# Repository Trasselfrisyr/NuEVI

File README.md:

### ⚠️ ORIGINAL REPO HAS BEEN MOVED TO BERGLUNDINST ORGANISATION ⚠️

This repository exists for archival purposes. Please update any references/links to https://github.com/berglundinst/NuEVI instead.

# NuEVI
A project by wind controller enthusiasts wanting to save the endangered Electronic Valve Instrument.

Follow the project at https://hackaday.io/project/25756-diy-evi-style-windcontroller

## Building NuEVI

NuEVI is easiest to build using the Arduino IDE. You will also need to download and install
[Teensyduino](https://www.pjrc.com/teensy/td_download.html) to build for and upload to the Teensy.

### Libraries

A few libraries need to be added that are not part of the default Arduino install. These can be
added directly via the Library Manager in the Arduino IDE:
* Adafruit MPR121
* Adafruit GFX
* Adafruit SSD1306 (version 1.2.9 or above)
* NuEVI also includes on the [Filters](https://github.com/JonHub/Filters) library by Jonathan Driscoll, but that is no longer an external dependency.

### Compile options

Open NuEVI.ino in the Arduino IDE. Under "Tools -> Board", select "Teensy 3.2 / 3.1". Then set
"Tools -> USB Type" to "MIDI".

### Building and uploading

Connect the NuEVI via USB to your computer, open the Teensy application and make sure the "Auto"
option is selected (the green round icon). In Arduino IDE, select "Sketch -> Verify/Compile" and
once that is complete press the reset button on the Teensy chip (you have to remove the top cover
on the NuEVI to access this). Upon resetting, it should upload the new firmware onto the NuEVI.

After uploading new firmware, you may need to reset the config memory of the NuEVI. To do this, press
and hold the MENU and ENTER buttons while turning on the NuEVI. Note that this resets all sensor calibrations too. For new versions this should not be neccessary, as value and version checks are in place.

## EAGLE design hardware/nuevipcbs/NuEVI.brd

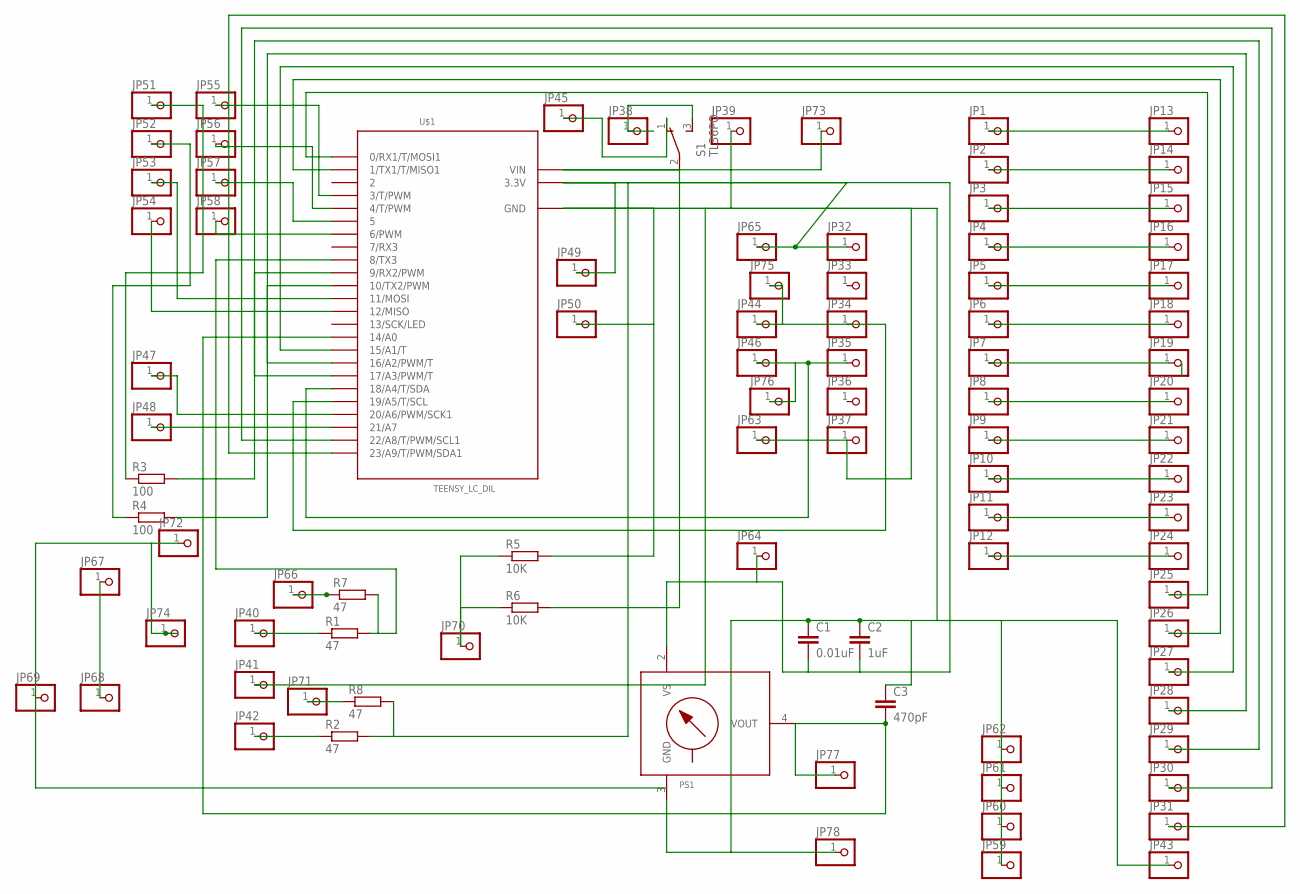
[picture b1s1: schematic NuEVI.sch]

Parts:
C1: 0.01uF; C050-024X044
C2: 1uF; C050-024X044
C3: 470pF; C050-024X044
JP1, JP2, JP3, JP4, JP5, JP6, JP7, JP8, JP9, JP10, JP11, JP12, JP13, JP14, JP15, JP16, JP17, JP18, JP19, JP20, JP21, JP22, JP23, JP24, JP25, JP26, JP27, JP28, JP29, JP30, JP31, JP32, JP33, JP34, JP35, JP36, JP37, JP38, JP39, JP40, JP41, JP42, JP43, JP44, JP45, JP46, JP47, JP48, JP49, JP50, JP51, JP52, JP53, JP54, JP55, JP56, JP57, JP58, JP59, JP60, JP61, JP62, JP63, JP64, JP65, JP66, JP67, JP68, JP69, JP70, JP71, JP72, JP73, JP74, JP75, JP76, JP77, JP78: PINHD-1X1; 1X01
PS1: MPX-1369; 1369
R1, R2, R7, R8: 47; 0207/7
R3, R4: 100; 0207/7
R5, R6: 10K; 0207/7
S1: TL36PO; TL3XPO
U$1: TEENSY_LC_DIL; TEENSY_3.0-3.2&LC_DIL

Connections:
GND: C1.1, C2.1, C3.1, JP37.1, JP39.1, JP41.1, JP43.1, JP50.1, JP59.1, JP60.1, JP61.1, JP62.1, JP63.1, JP69.1, JP72.1, JP74.1, JP78.1, PS1.3 (GND), R5.2, U$1.AGND (GND), U$1.GND
unnamed: JP1.1, JP13.1
unnamed: JP2.1, JP14.1
unnamed: JP3.1, JP15.1
unnamed: JP4.1, JP16.1
unnamed: JP5.1, JP17.1
unnamed: JP6.1, JP18.1
unnamed: JP7.1, JP19.1
unnamed: JP8.1, JP20.1
unnamed: JP9.1, JP21.1
unnamed: JP10.1, JP22.1
unnamed: JP11.1, JP23.1
unnamed: JP25.1, U$1.0 (0/RX1/T/MOSI1)
unnamed: JP12.1, JP24.1
unnamed: JP26.1, U$1.1 (1/TX1/T/MISO1)
unnamed: JP27.1, U$1.15/A1 (15/A1/T)
unnamed: JP28.1, U$1.16/A2 (16/A2/PWM/T)
unnamed: JP29.1, U$1.17/A3 (17/A3/PWM/T)
unnamed: JP30.1, U$1.22/A8 (22/A8/T/PWM/SCL1)
unnamed: JP31.1, U$1.23/A9 (23/A9/T/PWM/SDA1)
unnamed: C1.2, C2.2, JP32.1, JP49.1, JP64.1, JP65.1, PS1.2 (VS), R2.2, R8.2, U$1.3.3V
unnamed: JP47.1, U$1.20/A6 (20/A6/PWM/SCK1)
unnamed: JP34.1, JP44.1, JP75.1, U$1.19/A5 (19/A5/T/SCL)
unnamed: JP35.1, JP46.1, JP76.1, U$1.18/A4 (18/A4/T/SDA)
unnamed: JP38.1, S1.3 (S)
unnamed: R1.2, R7.2, U$1.8 (8/TX3)
unnamed: JP40.1, R1.1
unnamed: JP42.1, R2.1
unnamed: C3.2, JP77.1, PS1.4 (VOUT), U$1.14/A0
unnamed: JP73.1, R6.2, S1.2, U$1.VIN
unnamed: JP48.1, U$1.21/A7
unnamed: JP51.1, R3.1
unnamed: JP52.1, R4.1
unnamed: JP53.1, U$1.11 (11/MOSI)
unnamed: JP54.1, U$1.12 (12/MISO)
unnamed: JP55.1, U$1.3 (3/T/PWM)
unnamed: JP56.1, U$1.4 (4/T/PWM)
unnamed: JP57.1, U$1.5
unnamed: JP58.1, U$1.6 (6/PWM)
unnamed: JP45.1, S1.1 (O)
unnamed: R4.2, U$1.10 (10/TX2/PWM)
unnamed: JP67.1, JP68.1
unnamed: R3.2, U$1.9 (9/RX2/PWM)
unnamed: JP70.1, R5.1, R6.1
unnamed: JP71.1, R8.1
unnamed: JP66.1, R7.1

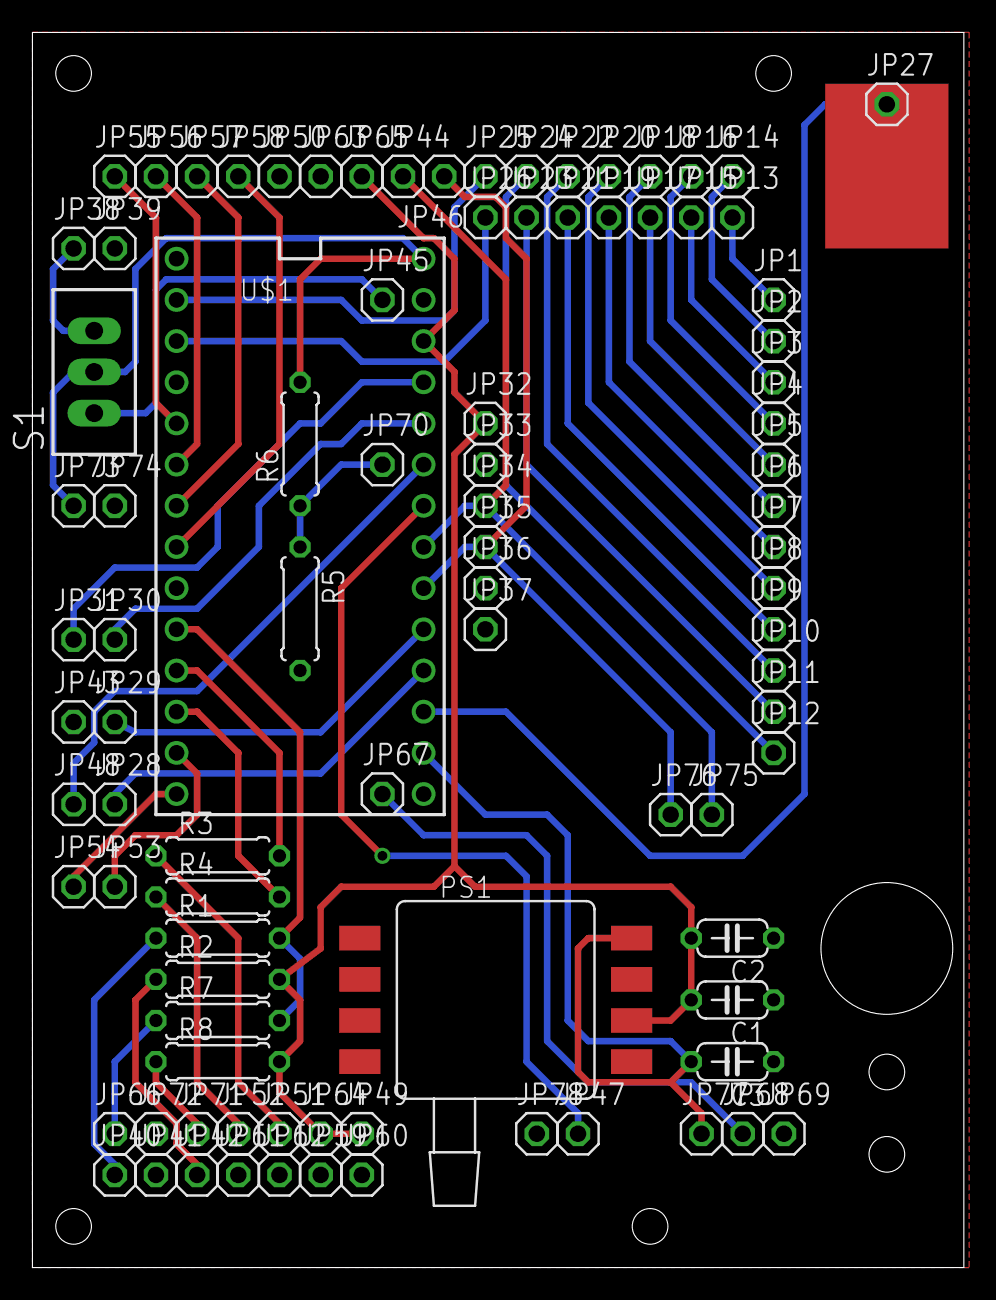
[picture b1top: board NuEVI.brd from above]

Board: 2 copper layers, 57.5 x 76.2 mm, 92 parts (0 on the bottom side), 46 nets.

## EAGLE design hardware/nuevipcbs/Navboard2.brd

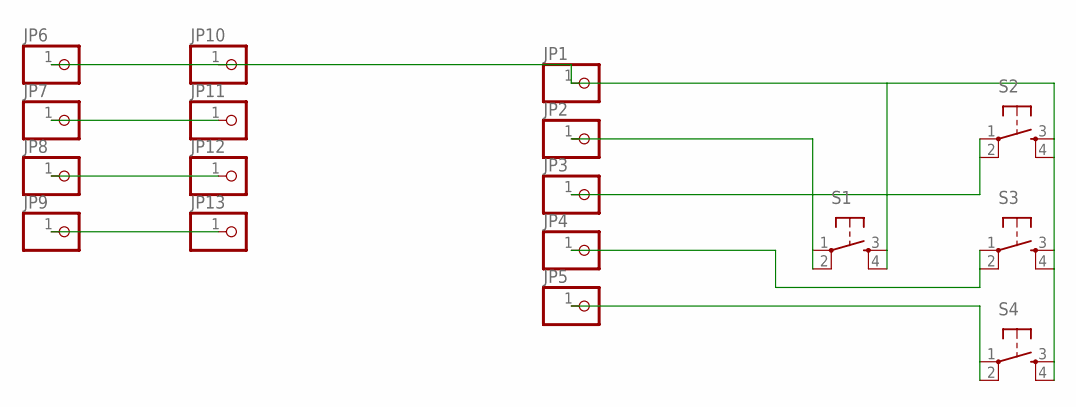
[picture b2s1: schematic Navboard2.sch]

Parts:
JP1, JP2, JP3, JP4, JP5, JP6, JP7, JP8, JP9, JP10, JP11, JP12, JP13: PINHD-1X1; 1X01
S1, S2, S3, S4: TAC_SWITCHPTH; TACTILE-PTH

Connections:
GND: JP1.1, JP6.1, JP10.1, S1.3, S1.4, S2.3, S2.4, S3.3, S3.4, S4.3, S4.4
unnamed: JP2.1, S1.1, S1.2
unnamed: JP3.1, S2.1, S2.2
unnamed: JP4.1, S3.1, S3.2
unnamed: JP5.1, S4.1, S4.2
unnamed: JP7.1, JP11.1
unnamed: JP8.1, JP12.1
unnamed: JP9.1, JP13.1

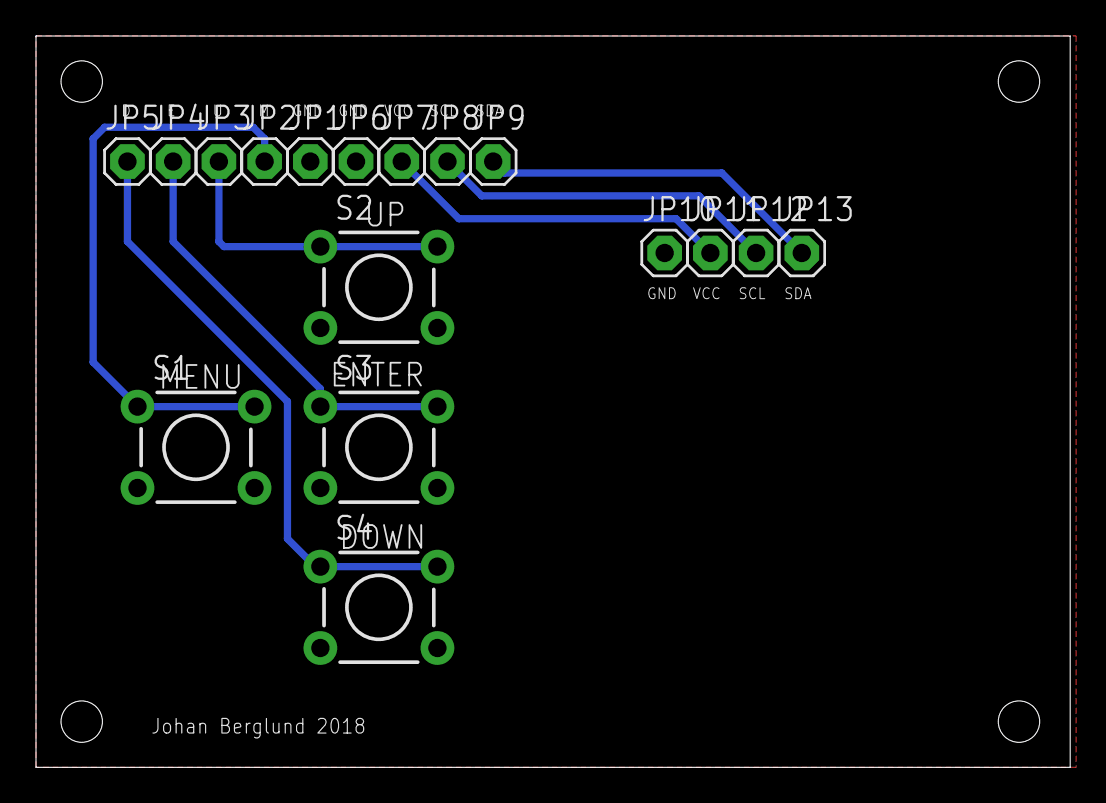
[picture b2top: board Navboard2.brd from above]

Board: 2 copper layers, 57.5 x 40.6 mm, 17 parts (0 on the bottom side), 8 nets.

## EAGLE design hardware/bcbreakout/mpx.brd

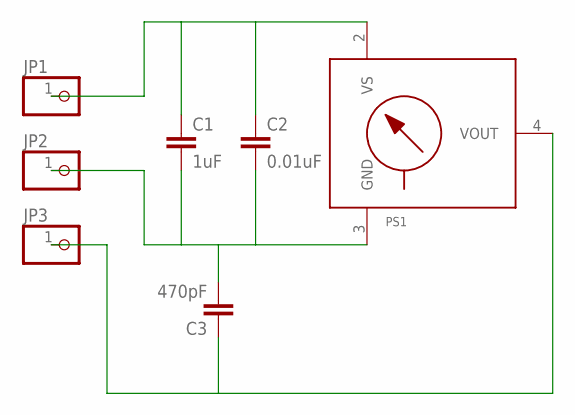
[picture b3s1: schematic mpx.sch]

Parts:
C1: 1uF; C050-024X044
C2: 0.01uF; C050-024X044
C3: 470pF; C050-024X044
JP1, JP2, JP3: PINHD-1X1; 1X01
PS1: MPX-1369; 1369

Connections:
GND: C1.2, C2.2, C3.2, JP2.1, PS1.3 (GND)
unnamed: C3.1, JP3.1, PS1.4 (VOUT)
unnamed: C1.1, C2.1, JP1.1, PS1.2 (VS)

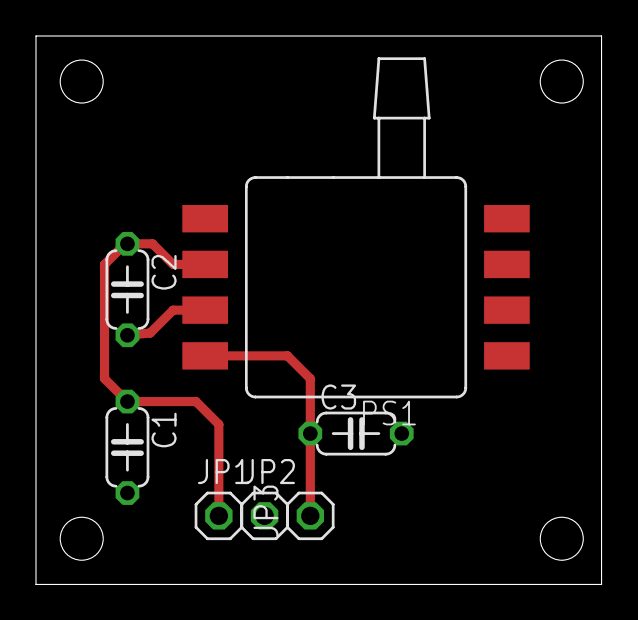
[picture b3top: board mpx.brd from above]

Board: 2 copper layers, 31.4 x 30.5 mm, 7 parts (0 on the bottom side), 3 nets.

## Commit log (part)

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2017-08-08 First commit. Arduino sketch plus devboard plans.
2017-08-09 Added the option to have the vibrato go down first, then up.
2017-08-26 Added untested version with menu system and other added features. Preview.
2017-08-29 Bugfixes galore. Added sensor level indicators in sensor adjust settings. Added MIDI note range check with octave repeat.
2017-09-09 Disabled baseline tracking for the MPR121. Added status LEDs for breath and bite (portamento).
2017-09-11 More work on the vibrato. Fixed sending program change to wrong channel on DIN MIDI. Pitchbend start value fix.
2017-09-16 Breath reading changed from 10 bit to 12 bit. Added hi res midi on cc#1 (mod) and an option to compile with breath CV output on DAC pin. Special key functions implemented (slur sustain, parallel chor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
2017-09-23 Just forgot a thing for the slurred note velocity.
2017-10-03 Added more breath response curve options.
2017-10-05 Adjusted some curves where values were a bit off. Replaced the S-curves with less dramatic ones. Added a fourth one.
2018-02-28 Added battery voltage meter (matched 10K resistors to A11 from AGND and VIN). Added CC#74 as option for extra controller. Added velocity sample delay setting and velocity bias setting. Removed midi p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
2018-04-19 Got the more advanced breath signal filtering working. (Still some commented out crap in there from testing/comparing. Just ignore it.) Fixed some errors in curves.
2018-05-25 Added chord rotator function. Added setting for mono voice note during chord play. Minor enhancements in FastPatch functionality. Bug fix for storing AT setting.
2018-08-27 New and improved vibrato. Added vibrato menu for setting depth, sensitivity and zero return speed. Added Gate Hold function. Added negative pressure trig for legacy instant settings functionality. Bu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
2018-08-28 Update readme
    Add notice about resetting EEPROM config.
2018-09-01 Added item in vibrato menu for setting squelch level for vibrato sensor (noise filtering/dead zone). Added setting for vibrato direction.
2018-09-03 Use defines instead of hardcoded pin numbers Also automatic "dangling whitespace" cleanup
2018-09-03 Check for exact display type instead of just height
2018-09-03 Refactor factory reset for clarity
2018-10-22 Version 1.2.7
2018-10-27 Version 1.2.9
    * Fix for pitch bend summing near zero.
    * Deglitch setting now in steps of 1ms
    * Velocity sample delay setting now in steps of 1ms
2018-12-28 Added anti-glitch for top roller when in bottom octave. Added individual note-offs efter All Notes Off at MIDI Panic (to work in Logic and other software not recognizing the regular All Notes Off).
2019-03-02 Use midi serial definition from proper place
2019-03-02 A whiter shade of space
2019-03-02 Constrain unconstrained non-use of constrain()
2019-03-04 Output breath sensor value on DAC (from Johan)
2019-03-04 Move all source files to subdirectory to be less confusing for Arduino IDE
2019-03-04 Rename non-main ino files to cpp
2019-03-05 Let us not rename files right now.
    This reverts commit 347b6e5c71ea4c537caaec08537b96d3f825ece0.
2019-03-21 Cleanup
2019-06-03 Renamed menu.ino to menu.cpp
    This change required lots of other changes to have it compile. I had to declare all variables from NuEVI.ino used by the menu as extern in a separate header file (globals.h).
    Also I moved all defines from NuEVI.ino to a config.h file. I think some of these could be moved back or even moved into menu.cpp.
    I declared many variables and functions in menu.cpp as static and moved them around to avoid forward declarations. For simplicity I did some forward declarations anyway.
    Some varibles only used in menu.cpp was moved from NuEVI.ino instead of having them as externals.
2019-06-07 Fix problem where the V was still visible if battery low
2019-06-08 Move access to usbMIDI to midi.ino
    NuEVI.ino shouldn’t have to know about usbMIDI.
2019-06-13 Simple simulation code
    Builds a native program on MacOS that runs the NuEVI firmware compiled for x86_64.
    Only input is arrow keys for menu buttons for now. Only output is console and display.
    Copied some more library files into the simulation folder, and renamed the modified *.cpp files from the libraries to *_sim.cpp.
2019-06-21 More inputs and outputs added in simulator
    * Set default value for battery sensor input
    * Show EEPROM values as unsigned.
    * Simulate K1 to K7 inputs (valve and trills++)
2019-06-21 Fixed spelling
2019-06-22 Initialize touch inputs to untouched
2019-06-23 Write new factor constants even if old version was < 24
    This bug would probably never happen in real life, and could be fix by holding down menu and enter buttons at startup. But a bug is a bug.
    The only reason I found this bug is that the simulator didn’t initialise EEPROM to 0xff, and even after I did that it crashed, because a version of 0xffff wasn't handled.
2019-06-23 Advanced unusage of parameters
2019-06-23 Minor cleanups
2019-06-23 Removed an unused function
2019-06-23 Menu selection is now data driven
    Some major refactoring has been going on.
    Added simple structs of data containing info about what action to take when a menu item is selected.
    Finally removed all but one call to display.display() in menu-function. There might still be more than one call to it on a frame though, since some functions still calls it internally.
2019-06-23 Use helper function for midi channel as well
2019-06-23 Handle sub menus in a generic way and moved adjust menu logic to separate file
    This is a big one where I can finally reap what I sown. Sub menu entries now provide two functions, one to get the text for the current value and one to apply changes aka save to EEPROM. With this I 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
    The question is still what to do with less general menus like the rotator and fast patch menu.
    One problem with the current implementation is that it is RAM heavy. It seems the const MenuEntry structs are placed
2019-06-23 Unified main and patch menu input handling
    Now all menu pages are handled the same way, which is great because now I can implement scrolling in the menu pages.
2019-06-23 Two unrelated changes
    * Move text print of submenu into function
    * No need to check if value changed since writeSettings uses EEPROM.update.
2019-06-23 Small bug fix
2019-06-23 Pass *currentPage to functions instead of the original page data
    This way it will be easier to break out even more functionality into more general functions.
2019-06-23 Moved over the rotation menu to new system
    Had to change how the values where stored in RAM from singed to unsigned to be able to use the generic menu features. Also had to add the MenuEntrySub as a parameter to the menu callback functions to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
    Did some major cleanup now that the special case of rotator menu is gone together with all uses of the old version of the sub menu struct.
2019-06-23 Converted more of the sub menus to the new sub definitions
    Found out that it’s the lambda functions used for pointer that forces the structs to be in ram instead or rom.
2019-06-23 Add argument parsing for eeprom stuff
2019-06-23 Converted lambdas to normal functions to save RAM
2019-06-24 EEPROM file storage, and argparsing that actually works
2019-06-24 Check for correct target platform and USB type
2019-06-24 Allow midi+serial usb type too (useful for "console debugging")
2019-06-24 Only write to file if value has actually changed.
2019-06-25 Annotate "fingering math" for readability
2019-06-25 Use pin names rather than hardcoding
2019-06-25 Removed switch statement for curves, use array lookup instead
2019-06-26 Fixed regression bug for patch select
    After the menu refactoring, switching patch with up/down buttons when screen was off didn't work correctly. Now it should work like before i.e. switch patch on first press of button and not requiring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
2019-06-27 Only handle scrolling if there are items to scroll
2019-07-15 EXTRAS menu page added, with items LEGACY PB, LEGACY BR, GATE HOLD and SPECIAL KEY to enable/disable these special functions.
2019-07-17 Flush screen buffer to the display in adjust menu
    The return value (that flagged for redraw) was ignored when handling input in the adjust menu.
2019-07-18 Removed SR and SR+ from CC list
2019-07-23 Remove global var for wireless power, add wl channel menu
2019-07-24 Added newer version hex files.
2019-07-25 Define constant for "dipswitch" positions
2019-07-25 Move EEPROM read/write functions to settings
2019-07-26 Simplify readSwitches()
2019-07-26 Mistakes were made
2019-07-27 Incorporate Filters code into NuEVI repo for smoother setup.
2019-07-28 Needs more whitespace
2019-07-30 Add facility to receive config via sysex
2019-08-04 Actually match teensy/arduino signatures
2019-08-05 Add functionality to use files as MIDI data to send to simulated device
2019-08-07 Try to core midi
2019-08-07 Make nuevisim compile again. And send midi noteOn.
2019-08-15 Proper bounds for breath cc value
2019-08-15 Simulator: Print out full sysex message, with very clever line ending
2019-08-21 Added AT (aftertouch) instead of OFF for Level control.
2019-08-26 Make Simulator Work Again
2019-09-17 Added latest NuEVI schematic, board and gerber files.
2019-10-16 Remove trailing whitespace
2019-10-16 touchValue never used here, no point in reading touch data.
2019-10-16 Avoid floating-point math for vibrato calculations
2019-10-20 Changed LVL/GLD controls to K6 (increase) and K5 (decrease) to lessen risk of accidental change. LED indicator fix for pinky portamento.
2019-10-22 Fix to get the new pitchlatched patch change the same values as the other legacy ones.
2019-12-11 Now it's also NuRAD firmware! Set define for compile option NURAD in hardware.h to switch. Added a new little thing for NuEVI too: releasing the rollers leaves octave in current one instead of going 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
2020-02-24 New settings for better portamento performance on Roland SE-02. SEL for switching between OFF and LIN, SEE for switching between OFF and EXP.
2020-04-27 Added battery type setting and detailed battery info in ABOUT menu (support for NiMH and LiPo batteries). Added lip sensor activated harmonic series, with settings for range and series type. Added Nu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
2020-06-04 Fix for SAX fingering and updated fingering chart (NuRAD). Experimental fingerings using rollers for harmonic series (NuEVI). LED indication for extra controller sensor and startup LED check and also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
2020-07-22 NuEVI and NuRAD: Timing and speed issue solved - SSD1306 display library needed editing to prevent it from lowering I2C bus speed. Added setting to enable/disable the on the fly key switching. NuRAD: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
2020-08-19 * Adjustment setting for thumb lever (for optimizing thumb portamento control). By setting THR (level of push force to activate) and MAX (level of push force to achieve maximum set portamento) values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
    * Glide setting SWO, SWitching Only, sending only Glide on/off (CC#65) for use with synths where glide rate CC#5 is used in non standard ways, for example some DSI/Sequential synths like the Prophet 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
2020-10-10 * Changed names for ADJUST page titles (to shorten) and added numerical value readouts for THR and MAX settings. * Corrected start position for rotators and added reset to first position when activat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
2021-01-01 Editing SSD1306 library for I2C speed no longer neccessary.
2021-02-20 * Added three new settings in EXTRAS MENU – CV TUNE, CV SCALE and CV EC LFO. The first two allow for software tuning of the CV output for 1V/Oct when using NuEVI CV, NuEVI Plus or NuEVI/NuRAD with ex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
2021-03-16 Increased range of CV tuning and scaling.
2021-07-09 * New quarter tone setting for Pinky Key (NuEVI) and Mod Key (NuRAD) – QTN. This makes the Pinky/Mod key a key for playing one quarter tone down using pitchbend (MIDI) or directly affecting the built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
    * Changes to extra controller harmonics settings (experimental). Reverse direction options (ending with an ‘R’) available following the ones goin
2023-02-27 Changes up to 1.6.0
2023-02-28 Removed overly complex logic
    The `leverIsOn` and `biteIsOn` variables were only used inside their
    respective functions, and could be removed completely.
2023-05-03 Made platformio config work (on my system)
    I hope it works for everyone else as well.
2024-02-29 PlatformIO Teensy 4.0 build
2024-03-06 Fix for CV glide and vibrato in combination
2024-08-03 add VIB+ option (send both VIB and CC) for biteControl
2024-11-02 Keys2CCs initial commit
2025-07-24 Added sure y/n for factory reset.
2026-03-12 Replace preprocessor "or" with "||" everywhere
2026-03-13 Accept c01 (what device sends to computer) and c02 (what computer normally sends) as incoming config, to accept "our own sysex dumps" (if using separate tool, not config UI).
2026-03-14 Ignore vscode stuff
2026-03-14 Get simulator up and running again
    Only tested on linux this time around. With some luck it will still build on macos. I will put a minimal amount of effort to get it working on macos.

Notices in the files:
parts and their libraries:
SparkFun-Retired: Licensing: Creative Commons ShareAlike 4.0 International - https://creativecommons.org/licenses/by-sa/4.0
